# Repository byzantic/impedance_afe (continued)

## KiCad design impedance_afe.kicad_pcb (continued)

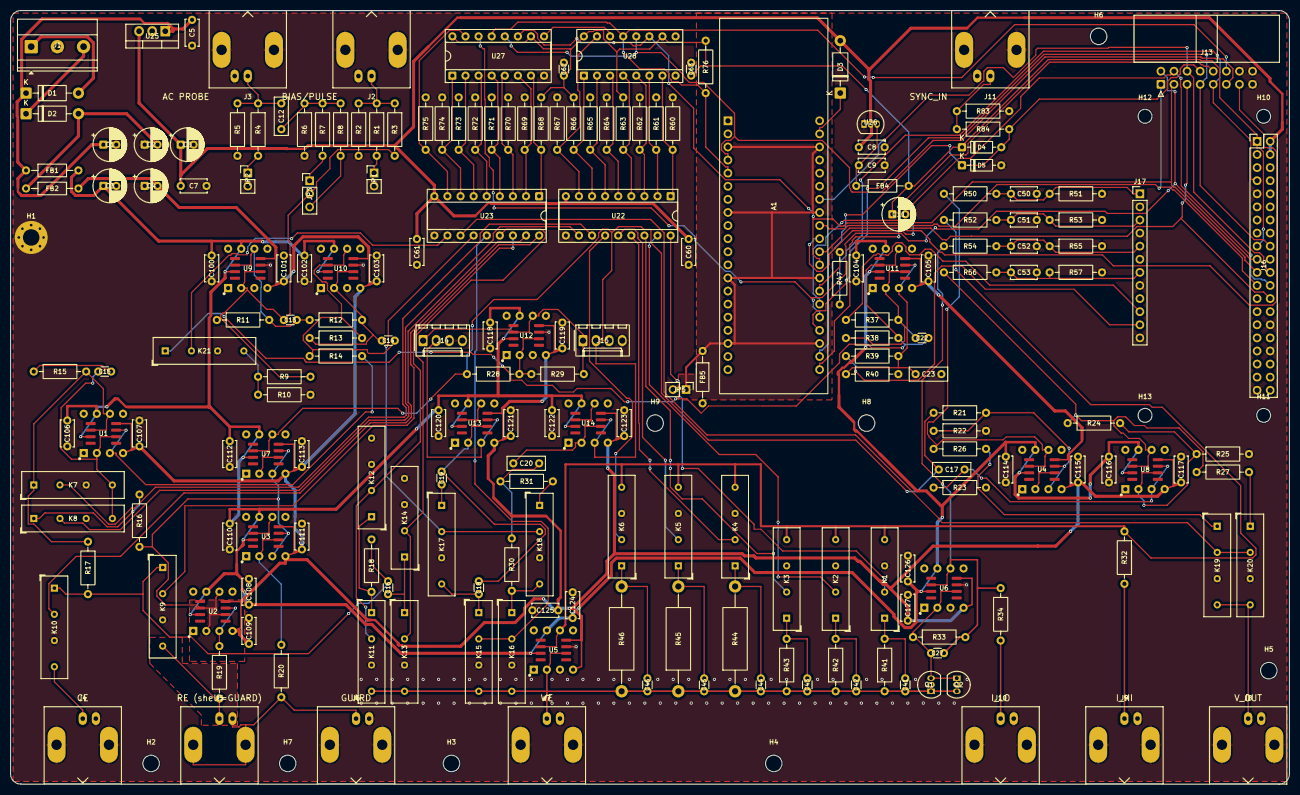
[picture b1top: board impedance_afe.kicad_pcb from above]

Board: 2 copper layers, 248.0 x 150.0 mm, 222 parts (0 on the bottom side), 127 nets.

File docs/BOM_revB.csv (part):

Designators,Qty,Value,Debug build,Precision build,Footprint,MPN / notes,LCSC,DNP
A1,1,Raspberry Pi Pico 2,Raspberry Pi Pico 2,Raspberry Pi Pico 2,Pico2_ESP32-S3-ETH_THT,"SC1631 (Pico 2) or Waveshare ESP32-S3-ETH, on 2x 1x20 sockets",,
"C1,C2",2,47u/35V,47u/35V,47u/35V,CP_Radial_D6.3mm_P2.50mm,,,
"C3,C4",2,10u/35V,10u/35V,10u/35V,CP_Radial_D6.3mm_P2.50mm,,,
C5,1,330n,330n,330n,C_Disc_D5.0mm_W2.5mm_P5.00mm,,,
C6,1,10u/25V,10u/25V,10u/25V,CP_Radial_D6.3mm_P2.50mm,,,
"C7,C60,C61,C100,C101,C102,C103,C104,C105,C106,C107,C108,C109,C110,C111,C112,C113,C114,C115,C116,C117,C118,C119,C120,C121,C122,C123,C124,C125,C126,C127",31,100n,100n,100n,C_Disc_D5.0mm_W2.5mm_P5.00mm,,,
"C8,C9",2,1u,1u,1u,C_Disc_D5.0mm_W2.5mm_P5.00mm,,,
C11,1,10u/16V,10u/16V,10u/16V,CP_Radial_D6.3mm_P2.50mm,,,
C12,1,1u film,1u film,1u film,C_Rect_L7.2mm_W2.5mm_P5.00mm_FKS2_FKP2_MKS2_MKP2,,,
"C13,C14",2,10p C0G,10p C0G,10p C0G,C_Disc_D3.0mm_W1.6mm_P2.50mm,,,
C15,1,100p C0G,100p C0G,100p C0G,C_Disc_D3.0mm_W1.6mm_P2.50mm,,,
"C16,C18",2,100p 1% C0G,100p 1% C0G,100p 1% C0G,C_Disc_D3.0mm_W1.6mm_P2.50mm,,,
C17,1,15n film,15n film,15n film,C_Rect_L7.2mm_W2.5mm_P5.00mm_FKS2_FKP2_MKS2_MKP2,,,
C19,1,910p 1% C0G,910p 1% C0G,910p 1% C0G,C_Disc_D3.0mm_W1.6mm_P2.50mm,,,
C20,1,220n film,220n film,220n film,C_Rect_L7.2mm_W2.5mm_P5.00mm_FKS2_FKP2_MKS2_MKP2,,,
C22,1,22p C0G,22p C0G,22p C0G,C_Disc_D3.0mm_W1.6mm_P2.50mm,,,
C23,1,100n film,100n film,100n film,C_Rect_L7.2mm_W2.5mm_P5.00mm_FKS2_FKP2_MKS2_MKP2,,,
C27,1,68p C0G,68p C0G,68p C0G,C_Disc_D3.0mm_W1.6mm_P2.50mm,,,
C41,1,22p C0G,47p C0G,22p C0G,C_Disc_D3.0mm_W1.6mm_P2.50mm,,,
C42,1,10p C0G,15p C0G,10p C0G,C_Disc_D3.0mm_W1.6mm_P2.50mm,,,
C43,1,2.2p C0G,4.7p C0G,2.2p C0G,C_Disc_D3.0mm_W1.6mm_P2.50mm,,,
C44,1,1p C0G,1.5p C0G,1p C0G,C_Disc_D3.0mm_W1.6mm_P2.50mm,,,
C45,1,0.47p / gimmick,0.47p / gimmick,0.47p / gimmick,C_Disc_D3.0mm_W1.6mm_P2.50mm,,,DNP
C46,1,stray only,stray only,stray only,C_Disc_D3.0mm_W1.6mm_P2.50mm,,,DNP
"C50,C51,C52,C53",4,10n C0G,10n C0G,10n C0G,C_Disc_D5.0mm_W2.5mm_P5.00mm,,,
"C62,C63",2,100n,100n,100n,C_Disc_D3.0mm_W1.6mm_P2.50mm,,,
"D1,D2,D3",3,1N5819,1N5819,1N5819,D_DO-41_SOD81_P10.16mm_Horizontal,,,
"D4,D5",2,1N4148,1N4148,1N4148,D_DO-35_SOD27_P7.62mm_Horizontal,,,
"FB1,FB2,FB4,FB5",4,600R@100MHz,600R@100MHz,600R@100MHz,L_Axial_L5.3mm_D2.2mm_P10.16mm_Horizontal_Vishay_IM-1,,,
H1,1,M3,M3,M3,MountingHole_3.2mm_M3_Pad_Via,,,
"H2,H3,H4,H5,H6,H7,H8,H9",8,M3,M3,M3,MountingHole_3.2mm_M3,,,
"H10,H11,H12,H13",4,M2.5,M2.5,M2.5,MountingHole_2.7mm_M2.5,,,
J1,1,+15/GND/-15,+15/GND/-15,+15/GND/-15,"TerminalBlock_Phoenix_MKDS-1,5-3-5.08_1x03_P5.08mm_Horizontal",,,
J2,1,BIAS/PULSE,BIAS/PULSE,BIAS/PULSE,BNC_Amphenol_B6252HB-NPP3G-50_Horizontal,BNC R/A PCB 50R (Amphenol B6252HB-NPP3G-50 pattern),,
J3,1,AC_PROBE,AC_PROBE,AC_PROBE,BNC_Amphenol_B6252HB-NPP3G-50_Horizontal,BNC R/A PCB 50R (Amphenol B6252HB-NPP3G-50 pattern),,
J4,1,CE,CE,CE,BNC_Amphenol_B6252HB-NPP3G-50_Horizontal,BNC R/A PCB 50R (Amphenol B6252HB-NPP3G-50 pattern),,
J5,1,RE,RE,RE,BNC_Amphenol_B6252HB-NPP3G-50_Horizontal,BNC R/A PCB 50R (Amphenol B6252HB-NPP3G-50 pattern),,
J6,1,GUARD,GUARD,GUARD,BNC_Amphenol_B6252HB-NPP3G-50_Horizontal,BNC R/A PCB 50R (Amphenol B6252HB-NPP3G-50 pattern),,
J7,1,WE,WE,WE,BNC_Amphenol_B6252HB-NPP3G-50_Horizontal,BNC R/A PCB 50R (Amphenol B6252HB-NPP3G-50 pattern),,
J8,1,V_OUT,V_OUT,V_OUT,BNC_Amphenol_B6252HB-NPP3G-50_Horizontal,BNC R/A PCB 50R (Amphenol B6252HB-NPP3G-50 pattern),,
J9,1,I_HI,I_HI,I_HI,BNC_Amphenol_B6252HB-NPP3G-50_Horizontal,BNC R/A PCB 50R (Amphenol B6252HB-NPP3G-50 pattern),,
J10,1,I_LO,I_LO,I_LO,BNC_Amphenol_B6252HB-NPP3G-50_Horizontal,BNC R/A PCB 50R (Amphenol B6252HB-NPP3G-50 pattern),,
J11,1,SYNC_IN,SYNC_IN,SYNC_IN,BNC_Amphenol_B6252HB-NPP3G-50_Horizontal,BNC R/A PCB 50R (Amphenol B6252HB-NPP3G-50 pattern),,
J13,1,SPI/AUX,SPI/AUX,SPI/AUX,IDC-Header_2x08_P2.54mm_Horizontal,"2x8 shrouded box header, right angle",,
J14,1,POT C-null,POT C-null,POT C-null,Molex_KK-254_AE-6410-04A_1x04_P2.54mm_Vertical,Molex 22-27-2041 (KK 254); 0.1in header also fits,,
J15,1,POT G-null,POT G-null,POT G-null,Molex_KK-254_AE-6410-04A_1x04_P2.54mm_Vertical,Molex 22-27-2041 (KK 254); 0.1in header also fits,,
J16,1,ADC/DAC HAT (Pi 40-pin),ADC/DAC HAT (Pi 40-pin),ADC/DAC HAT (Pi 40-pin),PinHeader_2x20_P2.54mm_Vertical,,,
J17,1,ADC/DAC HAT analog,ADC/DAC HAT analog,ADC/DAC HAT analog,PinHeader_1x12_P2.54mm_Vertical,,,
"JP1,JP2",2,50R_TERM,50R_TERM,50R_TERM,PinHeader_1x02_P2.54mm_Vertical,,,
JP3,1,AC_GAIN x1/x0.1,AC_GAIN x1/x0.1,AC_GAIN x1/x0.1,PinHeader_1x03_P2.54mm_Vertical,,,
JP5,1,PICO_GND_TIE,PICO_GND_TIE,PICO_GND_TIE,PinHeader_1x02_P2.54mm_Vertical,,,
"K1,K2,K3,K4,K7,K8,K9,K10,K11,K13,K15,K16,K17,K18,K20,K21",16,SIP-1A05,SIP-1A05,SIP-1A05,Relay_SPST_StandexMeder_SIL_Form1A,Standex/Meder SIL05-1A72-71 or generic SIP-1A05,C7316298,
"K5,K6",2,SIP-1A05,SIP-1A05,Coto 9007-05-00 class (>=1e12 ohm; check footprint),Relay_SPST_StandexMeder_SIL_Form1A,Standex/Meder SIL05-1A72-71 or generic SIP-1A05,C7316298,
"K12,K14,K19",3,SIP-1B05 (NC),SIP-1B05,SIP-1B05,Relay_SPST_StandexMeder_SIL_Form1B,Standex/Meder SIL05-1B72-71,,
"Q1,Q2",2,2N3904 (C-B diode),2N3904 (C-B diode),2N3904 (C-B diode),TO-92_Inline,,,
"R1,R4,R20,R26,R27,R32,R34",7,49.9,49.9,49.9,R_Axial_DIN0207_L6.3mm_D2.5mm_P10.16mm_Horizontal,,,
"R2,R5,R10,R23,R83",5,100k,100k,100k,R_Axial_DIN0207_L6.3mm_D2.5mm_P10.16mm_Horizontal,,,
"R3,R7,R9,R11,R12,R13,R18,R21,R22,R28,R29,R37,R39",13,10k 0.1%,10k 0.1%,10k 0.1%,R_Axial_DIN0207_L6.3mm_D2.5mm_P10.16mm_Horizontal,,,
R6,1,1M,1M,1M,R_Axial_DIN0207_L6.3mm_D2.5mm_P10.16mm_Horizontal,,,
R8,1,100k 0.1%,100k 0.1%,100k 0.1%,R_Axial_DIN0207_L6.3mm_D2.5mm_P10.16mm_Horizontal,,,
"R14,R15",2,1k,1k,1k,R_Axial_DIN0207_L6.3mm_D2.5mm_P10.16mm_Horizontal,,,
"R16,R76,R84",3,10k,10k,10k,R_Axial_DIN0207_L6.3mm_D2.5mm_P10.16mm_Horizontal,,,
R17,1,47,47,47,R_Axial_DIN0207_L6.3mm_D2.5mm_P10.16mm_Horizontal,,,
R19,1,100,100,100,R_Axial_DIN0207_L6.3mm_D2.5mm_P10.16mm_Horizontal,,,
R24,1,9.09k 0.1%,9.09k 0.1%,9.09k 0.1%,R_Axial_DIN0207_L6.3mm_D2.5mm_P10.16mm_Horizontal,,,
"R25,R51,R53,R55,R57",5,1k 0.1%,1k 0.1%,1k 0.1%,R_Axial_DIN0207_L6.3mm_D2.5mm_P10.16mm_Horizontal,,,
R30,1,20k,20k,20k,R_Axial_DIN0207_L6.3mm_D2.5mm_P10.16mm_Horizontal,,,
R31,1,2.2k,2.2k,2.2k,R_Axial_DIN0207_L6.3mm_D2.5mm_P10.16mm_Horizontal,,,
R33,1,499 0.1%,499 0.1%,499 0.1%,R_Axial_DIN0207_L6.3mm_D2.5mm_P10.16mm_Horizontal,,,
"R38,R40",2,40.2k 0.1%,40.2k 0.1%,40.2k 0.1%,R_Axial_DIN0207_L6.3mm_D2.5mm_P10.16mm_Horizontal,,,
R41,1,1k 0.1%,1k 1% metal film,1k 0.1% metal foil,R_Axial_DIN0207_L6.3mm_D2.5mm_P10.16mm_Horizontal,,,
R42,1,10k 0.1%,10k 1% metal film,10k 0.1% metal foil,R_Axial_DIN0207_L6.3mm_D2.5mm_P10.16mm_Horizontal,,,
R43,1,100k 0.1%,100k 1% metal film,100k 0.1% metal foil,R_Axial_DIN0207_L6.3mm_D2.5mm_P10.16mm_Horizontal,,,
R44,1,1M 0.5%,1M 1% metal film,1M 0.5% glass high-megohm,R_Axial_DIN0414_L11.9mm_D4.5mm_P20.32mm_Horizontal,,,
R45,1,10M 1%,10M 1% metal film,10M 1% glass high-megohm,R_Axial_DIN0414_L11.9mm_D4.5mm_P20.32mm_Horizontal,,,
R46,1,100M 1%,100M 1% metal film,100M 1% glass high-megohm,R_Axial_DIN0414_L11.9mm_D4.5mm_P20.32mm_Horizontal,,,
R47,1,33,33,33,R_Axial_DIN0207_L6.3mm_D2.5mm_P10.16mm_Horizontal,,,
"R50,R52,R54,R56",4,4.02k 0.1%,4.02k 0.1%,4.02k 0.1%,R_Axial_DIN0207_L6.3mm_D2.5mm_P10.16mm_Horizontal,,,
"R60,R61,R62,R63,R64,R65,R66,R67,R68,R69,R70,R71,R72,R73,R74,R75",16,4.7k,4.7k,4.7k,R_Axial_DIN0207_L6.3mm_D2.5mm_P10.16mm_Horizontal,,,
"RV1,RV2",2,10k 10-turn panel,Bourns 3590S-2-103 panel + dial (off-board),Bourns 3590S-2-103 panel + dial (off-board),(off-board),,,
"U1,U2,U3,U5,U6,U7,U8,U13",8,OPA828/OPA134,OPA134PA,OPA828ID (SOIC) or OPA627AP (DIP),DIP-8_SOIC-8_Combo,,,
"U4,U9,U10,U11,U12,U14",6,OPA828/OPA134,OPA134PA,OPA134PA,DIP-8_SOIC-8_Combo,,,
"U22,U23",2,TBD62783APG,TBD62783APG,TBD62783APG,DIP-18_W7.62mm_Socket,,,
U25,1,L7805CV,L7805CV,L7805CV,TO-220-3_Vertical,,,
U26,1,MCP1700-3302E/TO,MCP1700-3302E/TO,MCP1700-3302E/TO,TO-92_Inline,,,
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
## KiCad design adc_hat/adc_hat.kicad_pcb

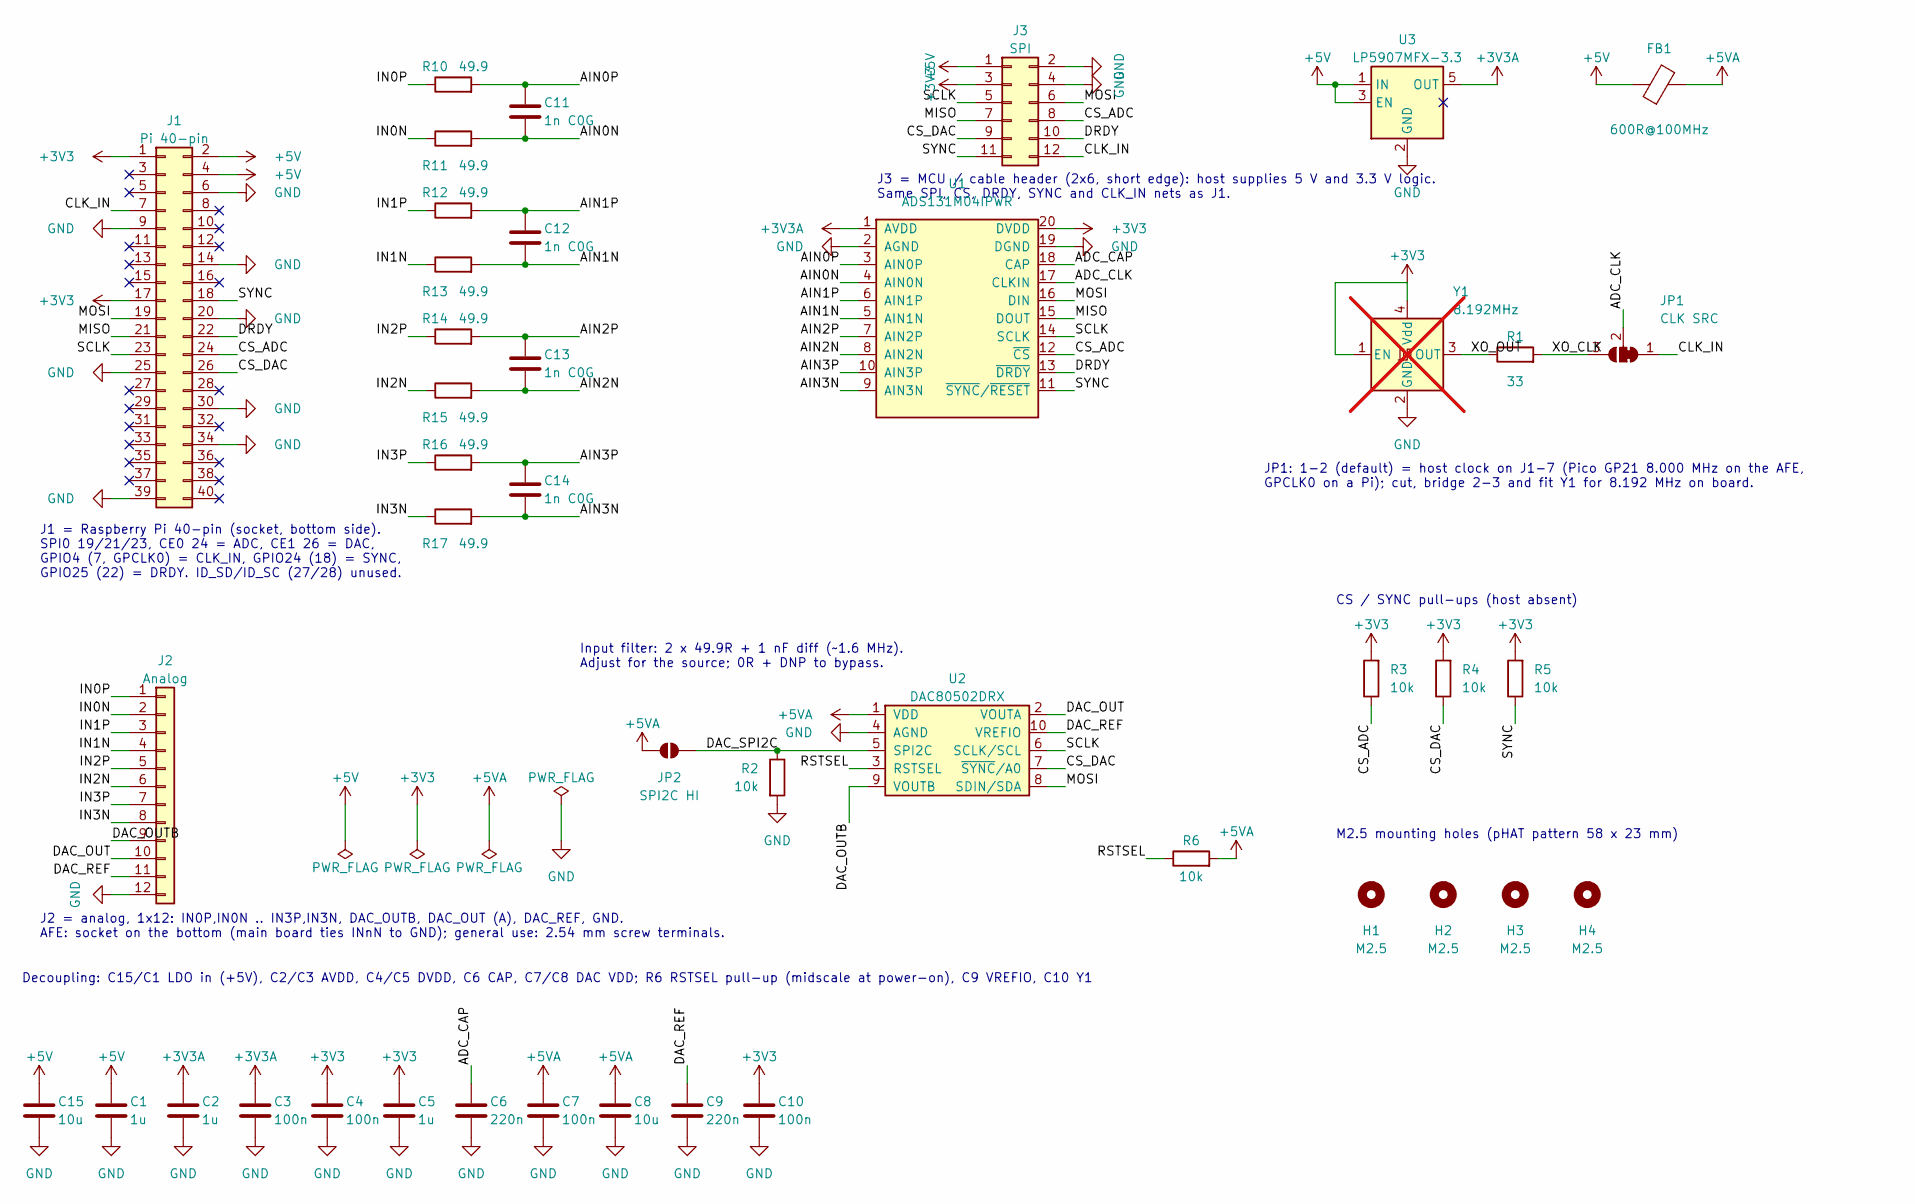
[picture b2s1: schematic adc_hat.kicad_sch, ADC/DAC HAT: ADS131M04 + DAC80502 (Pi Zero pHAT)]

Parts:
C1, C2, C5: 1u; C_0603_1608Metric; LCSC C15849
C3, C4, C7, C10: 100n; C_0603_1608Metric; LCSC C14663
C6, C9: 220n; C_0603_1608Metric; LCSC C21120
C8, C15: 10u; C_0805_2012Metric; LCSC C15850
C11, C12, C13, C14: 1n C0G; C_0603_1608Metric; MPN CC0603JRNPO9BN102; LCSC C106246
FB1: 600R@100MHz; L_0603_1608Metric; LCSC C1002
H1, H2, H3, H4: M2.5; MountingHole_2.7mm_M2.5
J1: Pi 40-pin; PinSocket_2x20_P2.54mm_Vertical; MPN 2x20 female 2.54 mm, 8.5 mm (Pi HAT sta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
J2: Analog; PinSocket_1x12_P2.54mm_Vertical; MPN 1x12 female 2.54 mm, 8.5 mm (AFE) or 2.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
J3: SPI; PinHeader_2x06_P2.54mm_Vertical; MPN 2x6 pin header 2.54 mm
JP1: CLK SRC; SolderJumper-3_P1.3mm_Bridged12_RoundedPad1.0x1.5mm
JP2: SPI2C HI; SolderJumper-2_P1.3mm_Open_RoundedPad1.0x1.5mm
R1: 33; R_0603_1608Metric; LCSC C23140
R2, R3, R4, R5, R6: 10k; R_0603_1608Metric; LCSC C25804
R10, R11, R12, R13, R14, R15, R16, R17: 49.9; R_0603_1608Metric; LCSC C23185
U1: ADS131M04IPWR; TSSOP-20_4.4x6.5mm_P0.65mm; MPN ADS131M04IPWR; LCSC C2862562
U2: DAC80502DRX; Texas_DRX_WSON-10_2.5x2.5mm_P0.5mm; MPN DAC80502DRXR; LCSC C1880990
U3: LP5907MFX-3.3; SOT-23-5; MPN LP5907MFX-3.3/NOPB; LCSC C80670
Y1: 8.192MHz; Oscillator_DIP-8_ASE-3.2x2.5_Combo; MPN 8.192 MHz 3.3 V CMOS XO: DIP-8 half-siz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; not fitted

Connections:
+3V3A: C2.1, C3.1, U1.1 (AVDD), U3.5 (OUT)
/ADC_CAP: C6.1, U1.18 (CAP)
/ADC_CLK: JP1.2 (C), U1.17 (CLKIN)
/AIN0N: C11.2, R11.2, U1.4 (AIN0N)
/AIN0P: C11.1, R10.2, U1.3 (AIN0P)
/AIN1N: C12.2, R13.2, U1.5 (AIN1N)
/AIN1P: C12.1, R12.2, U1.6 (AIN1P)
/AIN2N: C13.2, R15.2, U1.8 (AIN2N)
/AIN2P: C13.1, R14.2, U1.7 (AIN2P)
/AIN3N: C14.2, R17.2, U1.9 (AIN3N)
/AIN3P: C14.1, R16.2, U1.10 (AIN3P)
/CLK_IN: J1.7, J3.12, JP1.1 (A)
/CS_ADC: J1.24, J3.8, R3.1, U1.12 (~CS)
/CS_DAC: J1.26, J3.9, R4.1, U2.7 (~SYNC/A0)
/DAC_OUT: J2.10, U2.2 (VOUTA)
/DAC_OUTB: J2.9, U2.9 (VOUTB)
/DAC_REF: C9.1, J2.11, U2.10 (VREFIO)
/DAC_SPI2C: JP2.1 (A), R2.1, U2.5 (SPI2C)
/DRDY: J1.22, J3.10, U1.13 (~DRDY)
/IN0N: J2.2, R11.1
/IN0P: J2.1, R10.1
/IN1N: J2.4, R13.1
/IN1P: J2.3, R12.1
/IN2N: J2.6, R15.1
/IN2P: J2.5, R14.1
/IN3N: J2.8, R17.1
/IN3P: J2.7, R16.1
/MISO: J1.21, J3.7, U1.15 (DOUT)
/MOSI: J1.19, J3.6, U1.16 (DIN), U2.8 (SDIN/SDA)
/RSTSEL: R6.1, U2.3 (RSTSEL)
/SCLK: J1.23, J3.5, U1.14 (SCLK), U2.6 (SCLK/SCL)
/SYNC: J1.18, J3.11, R5.1, U1.11 (~SYNC/~RESET)
/XO_CLK: JP1.3 (B), R1.2
/XO_OUT: R1.1, Y1.3 (OUT)

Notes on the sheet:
J1 = Raspberry Pi 40-pin (socket, bottom side). SPI0 19/21/23, CE0 24 = ADC, CE1 26 = DAC, GPIO4 (7, GPCLK0) = CLK_IN, GPIO24 (18) = SYNC, GPIO25 (22) = DRDY. ID_SD/ID_SC (27/28) unused.
J2 = analog, 1x12: IN0P,IN0N .. IN3P,IN3N, DAC_OUTB, DAC_OUT (A), DAC_REF, GND. AFE: socket on the bottom (main board ties INnN to GND); general use: 2.54 mm screw terminals.
Input filter: 2 x 49.9R + 1 nF diff (~1.6 MHz). Adjust for the source; 0R + DNP to bypass.
JP1: 1-2 (default) = host clock on J1-7 (Pico GP21 8.000 MHz on the AFE, GPCLK0 on a Pi); cut, bridge 2-3 and fit Y1 for 8.192 MHz on board.
CS / SYNC pull-ups (host absent)
Decoupling: C15/C1 LDO in (+5V), C2/C3 AVDD, C4/C5 DVDD, C6 CAP, C7/C8 DAC VDD; R6 RSTSEL pull-up (midscale at power-on), C9 VREFIO, C10 Y1
M2.5 mounting holes (pHAT pattern 58 x 23 mm)
J3 = MCU / cable header (2x6, short edge): host supplies 5 V and 3.3 V logic. Same SPI, CS, DRDY, SYNC and CLK_IN nets as J1.

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
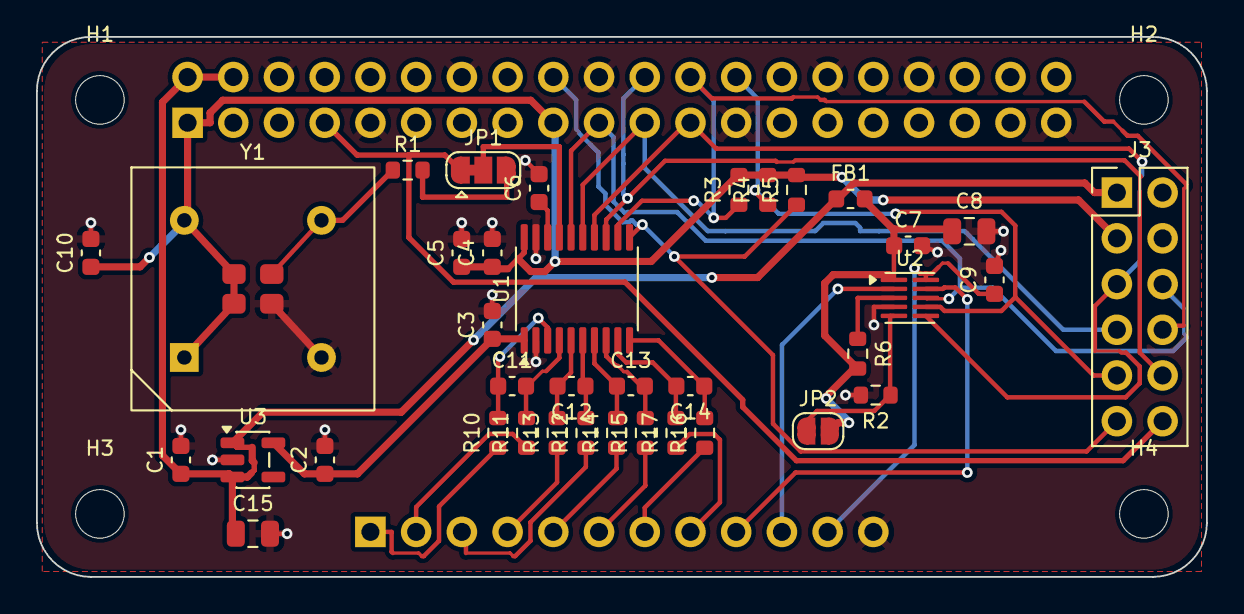
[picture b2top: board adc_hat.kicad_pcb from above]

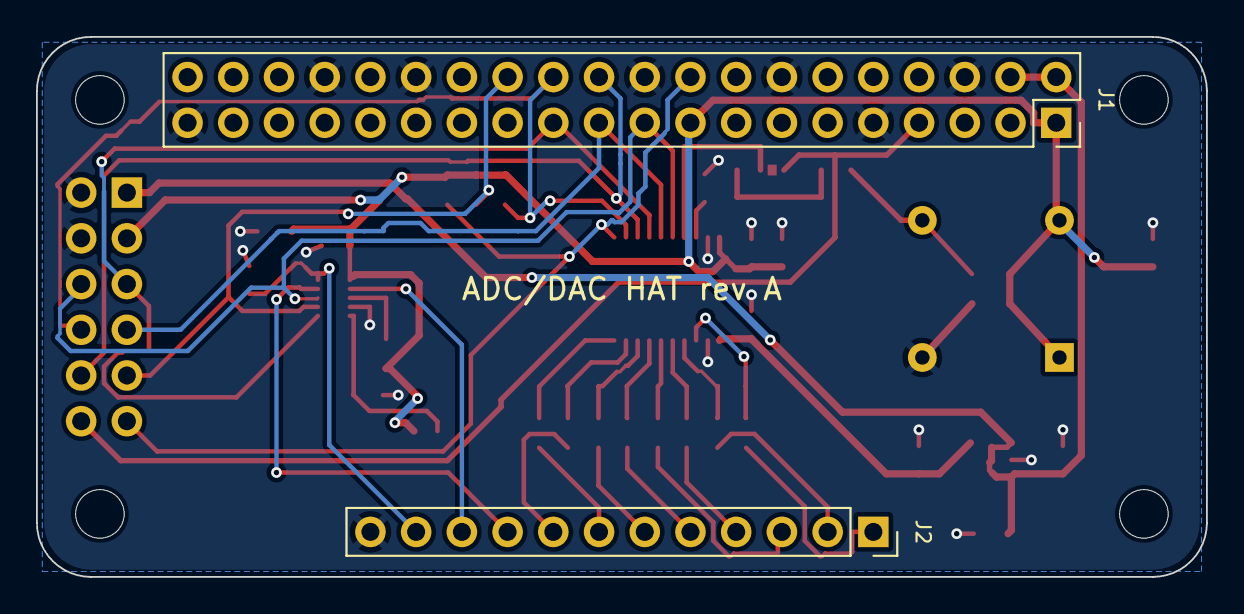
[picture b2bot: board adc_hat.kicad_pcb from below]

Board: 2 copper layers, 65.0 x 30.0 mm, 43 parts (2 on the bottom side), 38 nets.

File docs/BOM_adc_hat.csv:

Designators,Qty,Value,Footprint,MPN / notes,LCSC,DNP
"C1,C2,C5",3,1u,C_0603_1608Metric,,C15849,
"C3,C4,C7,C10",4,100n,C_0603_1608Metric,,C14663,
"C6,C9",2,220n,C_0603_1608Metric,,C21120,
"C8,C15",2,10u,C_0805_2012Metric,,C15850,
"C11,C12,C13,C14",4,1n C0G,C_0603_1608Metric,CC0603JRNPO9BN102,C106246,
FB1,1,600R@100MHz,L_0603_1608Metric,,C1002,
"H1,H2,H3,H4",4,M2.5,MountingHole_2.7mm_M2.5,,,
J1,1,Pi 40-pin,PinSocket_2x20_P2.54mm_Vertical,"2x20 female 2.54 mm, 8.5 mm (Pi HAT stacking height)",,
J2,1,Analog,PinSocket_1x12_P2.54mm_Vertical,"1x12 female 2.54 mm, 8.5 mm (AFE) or 2.54 mm screw terminals (general use)",,
J3,1,SPI,PinHeader_2x06_P2.54mm_Vertical,2x6 pin header 2.54 mm,,
JP1,1,CLK SRC,SolderJumper-3_P1.3mm_Bridged12_RoundedPad1.0x1.5mm,,,
JP2,1,SPI2C HI,SolderJumper-2_P1.3mm_Open_RoundedPad1.0x1.5mm,,,
R1,1,33,R_0603_1608Metric,,C23140,
"R2,R3,R4,R5,R6",5,10k,R_0603_1608Metric,,C25804,
"R10,R11,R12,R13,R14,R15,R16,R17",8,49.9,R_0603_1608Metric,,C23185,
U1,1,ADS131M04IPWR,TSSOP-20_4.4x6.5mm_P0.65mm,ADS131M04IPWR,C2862562,
U2,1,DAC80502DRX,Texas_DRX_WSON-10_2.5x2.5mm_P0.5mm,DAC80502DRXR,C1880990,
U3,1,LP5907MFX-3.3,SOT-23-5,LP5907MFX-3.3/NOPB,C80670,
Y1,1,8.192MHz,Oscillator_DIP-8_ASE-3.2x2.5_Combo,"8.192 MHz 3.3 V CMOS XO: DIP-8 half-size can, or 3.2 x 2.5 mm SMD (TBD)",,DNP
